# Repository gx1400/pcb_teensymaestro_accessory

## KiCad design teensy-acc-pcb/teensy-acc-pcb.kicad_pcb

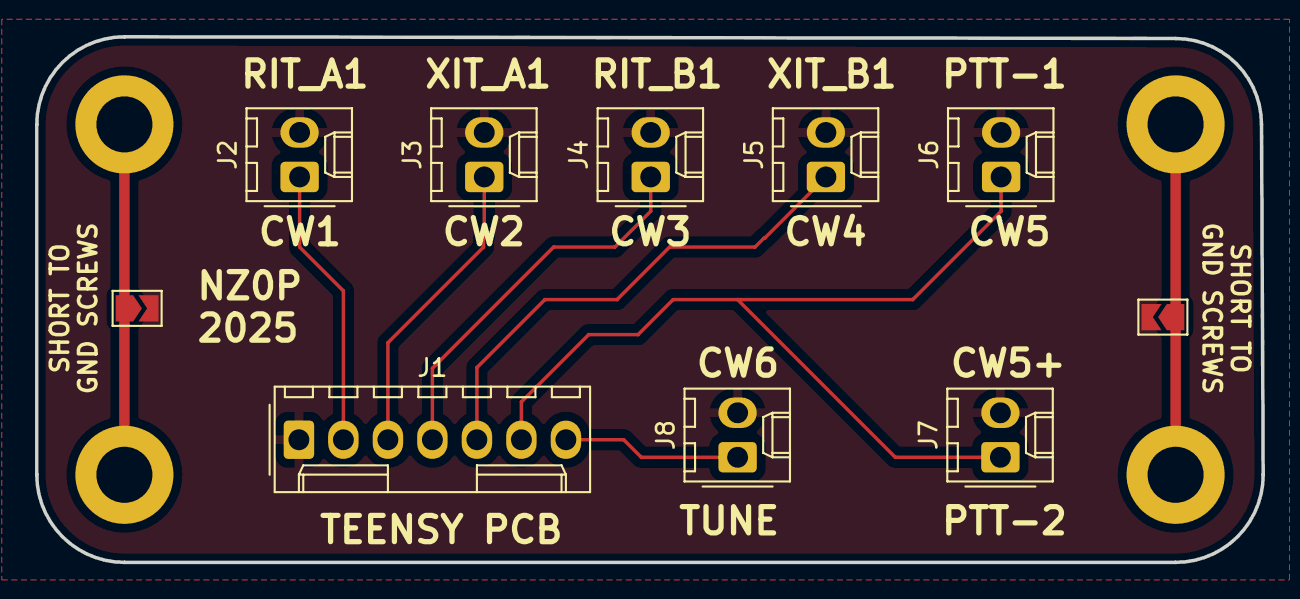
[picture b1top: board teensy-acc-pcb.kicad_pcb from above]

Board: 2 copper layers, 70.0 x 30.0 mm, 14 parts (0 on the bottom side), 9 nets.

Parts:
H1, H2, H3, H4: MountingHole_Pad; MountingHole_3.2mm_M3_DIN965_Pad
J1: Conn_01x07_Pin; Molex_KK-254_AE-6410-07A_1x07_P2.54mm_Vertical
J2, J3, J4, J5, J6, J7, J8: Conn_01x02_Pin; Molex_KK-254_AE-6410-02A_1x02_P2.54mm_Vertical
JP1, JP2: SolderJumper_2_Open; SolderJumper-2_P1.3mm_Open_TrianglePad1.0x1.5mm

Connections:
/PTT-CW5: J1.6, J6.1, J7.1
/RIT_A1-CW1: J1.2, J2.1
/RIT_B1-CW3: J1.4, J4.1
/TUNE-CW6: J1.7, J8.1
/XIT_A1-CW2: J1.3, J3.1
/XIT_B1-CW4: J1.5, J5.1
/hole1: H1.1, H2.1, JP1.1 (A)
/hole2: H3.1, H4.1, JP2.1 (A)
GND: J1.1, J2.2, J3.2, J4.2, J5.2, J6.2, J7.2, J8.2, JP1.2 (B), JP2.2 (B)

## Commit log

2025-01-28 commit ignore
2025-01-28 image
2025-01-28 fix link?
